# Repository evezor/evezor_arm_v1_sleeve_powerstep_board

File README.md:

# evezor_arm_v1_sleeve_powerstep_board

This board was intended to sit at the elbow of the robotic arm and serve as a power distribution point and a place to plug in extra stepper motors when extra axis are wanted.

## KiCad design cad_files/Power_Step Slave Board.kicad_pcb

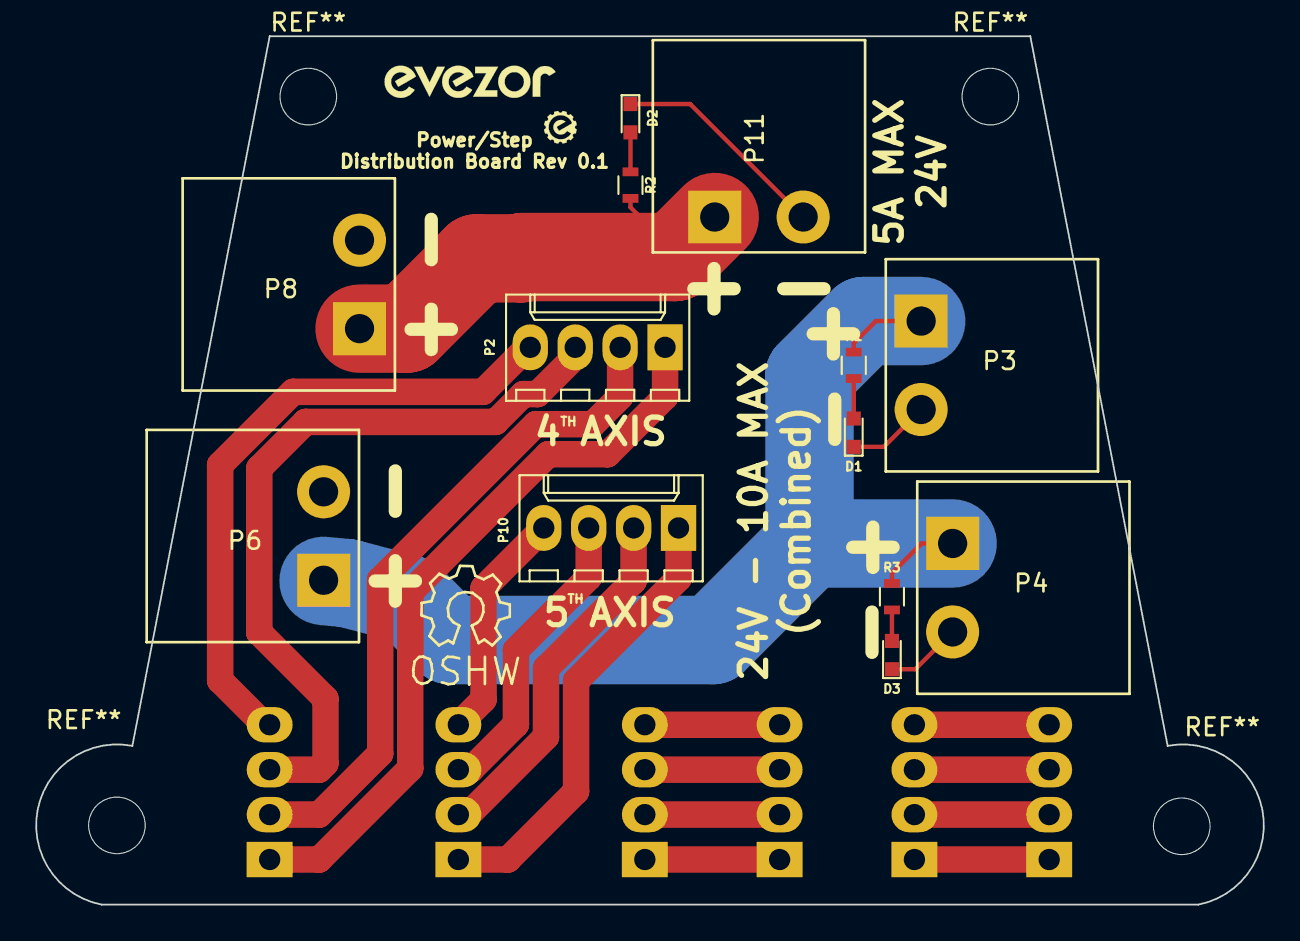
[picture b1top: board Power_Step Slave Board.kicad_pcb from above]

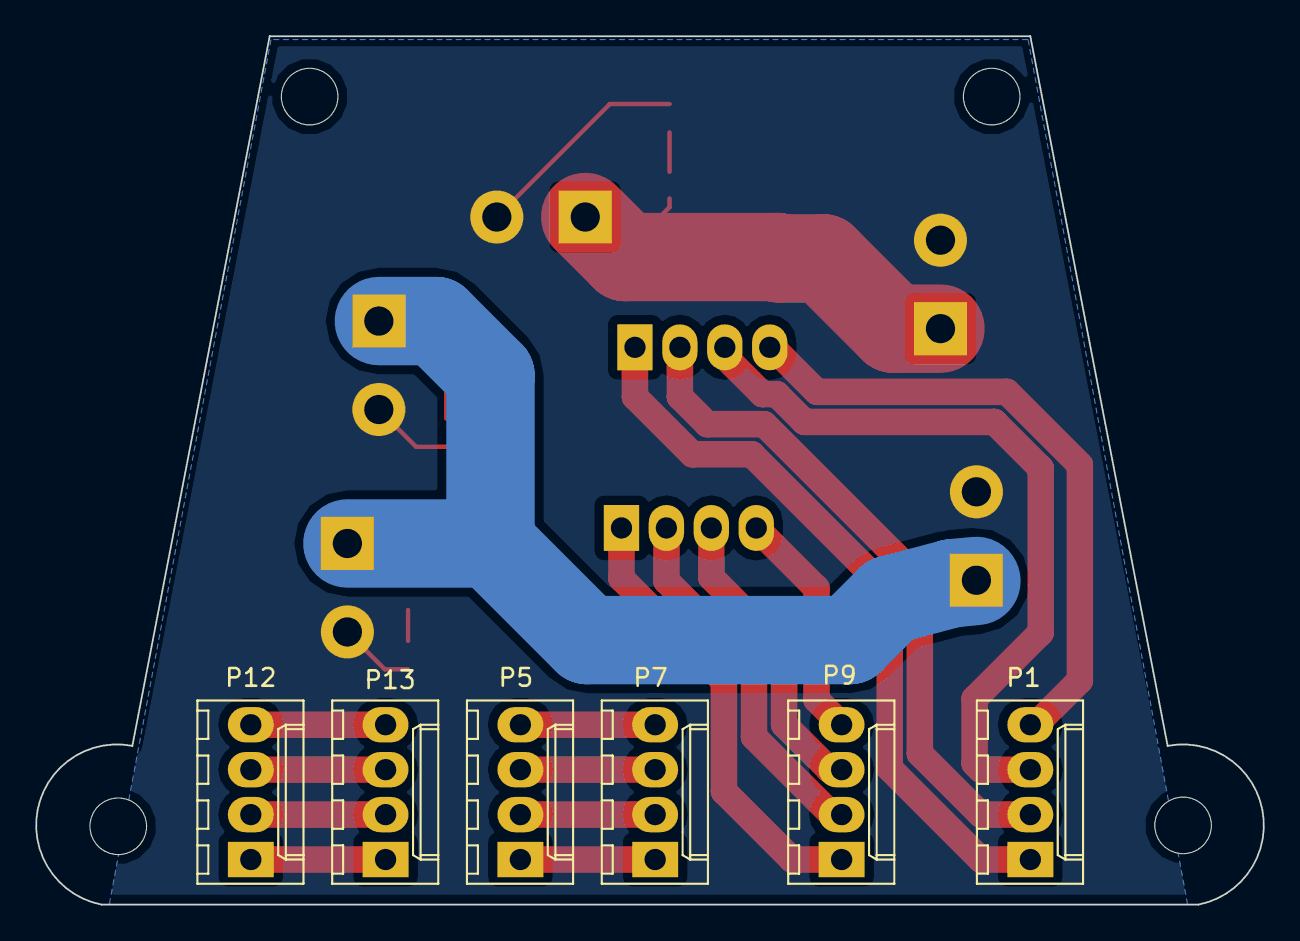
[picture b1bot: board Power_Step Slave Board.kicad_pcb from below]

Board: 2 copper layers, 69.4 x 49.1 mm, 19 parts (6 on the bottom side), 22 nets.

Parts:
D1, D2, D3: LED; LED_0603
P1, P2, P5, P7, P9, P10, P12, P13: CONN_01X04; Molex_KK-6410-04_04x2.54mm_Straight
P3, P4, P6, P8, P11: CONN_01X02; CONN_ON_SHORE_2x_15A
R1, R2, R3: R; R_0603

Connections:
GND: D1.1, D2.1, D3.1, P3.1, P4.1, P6.1, P8.1, P11.1
unnamed: D1.2, R1.1
unnamed: D2.2, R2.1
unnamed: D3.2, R3.1
unnamed: P1.1, P2.1
unnamed: P1.2, P2.2
unnamed: P1.3, P2.3
unnamed: P1.4, P2.4
unnamed: P3.2, P4.2, P6.2, R1.2, R3.2
unnamed: P5.1, P7.1
unnamed: P5.2, P7.2
unnamed: P5.3, P7.3
unnamed: P5.4, P7.4
unnamed: P9.1, P10.1
unnamed: P9.2, P10.2
unnamed: P9.3, P10.3
unnamed: P9.4, P10.4
unnamed: P8.2, P11.2, R2.2
unnamed: P12.1, P13.1
unnamed: P12.2, P13.2
unnamed: P12.3, P13.3
unnamed: P12.4, P13.4

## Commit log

2023-09-20 init
2023-10-03 add pics
